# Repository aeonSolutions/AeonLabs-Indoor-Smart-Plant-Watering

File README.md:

[ ](https://discord.gg/hw3j3RwfJf)

[PCB-Prototyping-Catalogue](https://github.com/aeonSolutions/PCB-Prototyping-Catalogue)  >>   [Home-Automation](https://github.com/aeonSolutions/PCB-Prototyping-Catalogue/tree/main/Home-Automation)  >>  [Safety & Health](https://github.com/aeonSolutions/AeonLabs-Safety-Health)    >>  Indoor Smart Plant Watering

⚠️ **Start by reading the documentation first**. [Click here to open it](https://github.com/aeonSolutions/AeonLabs-Safety-Health/wiki) 

# Indoor Smart Plant Watering

**The Problem**

Anyone loves to have some plants nearby, even when living in an apartment building. However, few know, or have devices to do proper indoor plant care. The main culprit is the absence of water and dry soil.

Furthermore, nowadays is commonly found online, when reading the news, another case and victim of light aggression, in particular, using some kind of diode laser light: red, green, yellow, or blue. And more dangerous, ultraviolet (UV) or infrared (IR) lasers.

**The Idea**

This Smart Indoor plant monitoring and watering is designed to be inserted into any indoor plant vase. Is able to measure and calculate the moisture content in the vase, and when detects low water contents, activates the water pump. Is able to connect to a local home server to upload indoor temperature, humidity, and air quality measurement data. This way, the owner, can have a history record database, without the need for expensive cloud subscriptions.  Additionally, it features a 6 LED system composed of an ultraviolet LED, an Infrared LED and an RGB LED, when combined with multiple devices like this one in the same room is able to perform some basic light aggression protection from an unknown light source outside during the night & day. 

If you prefer can read this project on Autodesk's Instructables.com website, [here](https://www.instructables.com/Indoor-Smart-Plant-Watering/).

<br>

### Status

 Fully tested and working

<br>

### Known PCB bugs
This public revision of the PCB electronics has a few known small errors. 

<br>

<p align="center">

<blockquote class="twitter-tweet"><p lang="en" dir="ltr">A small update on prototyping the indoor plant monitoring smart device <a href="https://twitter.com/gardein?ref_src=twsrc%5Etfw">@gardein</a> <a href="https://t.co/ORobUAjV0F">pic.twitter.com/ORobUAjV0F</a></p>&mdash; Aeonlabs.science (@AeonlabsS) </blockquote>
</p>

<br>

<br>

## Compatibility

<p align="center">

</p>

<br>

### Made by other Makers
 - [Soil Sensor](https://github.com/GewoonMaarten/soil-sensor) by [Maarten](https://github.com/GewoonMaarten)

<br>

## What one additionally needs
- [USB to UART/USB TTL firmware burner for 5V and 3.3V MCUs ](https://github.com/aeonSolutions/PCB-Prototyping-Catalogue/blob/main/DIY-Maker/README.md) 
<br />
<br />

**Get a Notification on every PCB update**

|  | You can fill in your [email here (Google form)](https://docs.google.com/forms/d/e/1FAIpQLScErMgQYRdA-umvCjvTPPrCO7Lg1QYowTxb7vfa8cTfrcPEAA/viewform?usp=pp_url) and I'll send a reminder when a new PCB prototype is made available here or a new revision for an existing PCB. Stay tuned! |
|-------------|------|

<br />

## Buy the PRO version on Tindie

|  | To all those not into electronics and still liked and want to own any of the listed PCB for smart devices can buy the PRO version on Tindie ready to install and use. |
|-------------|------|

### Useful links 
Below is a list of links with useful information about these kinds of abusive and many times criminal and terrorist usages.
[continue reading ...](https://github.com/aeonSolutions/AeonLabs-Safety-Health/wiki/Useful-Links)

<br />
<br />

**Get a Notification on every PCB update**

|  | You can fill in your [email here (Google form)](https://docs.google.com/forms/d/e/1FAIpQLScErMgQYRdA-umvCjvTPPrCO7Lg1QYowTxb7vfa8cTfrcPEAA/viewform?usp=pp_url) and I'll send a reminder when a new PCB prototype is made available here or a new revision for an existing PCB. Stay tuned! |
|-------------|------|

<br>

**Hire AeonLabs** <br>
If you like my work here and are looking to design and deploy your own smart device find [here](https://github.com/aeonSolutions/PCB-Prototyping-Catalogue/wiki/How-to-Hire-AeonLabs) how to hire me. 

<br>

## Author

You can get in touch with me on my LinkedIn Profile:

#### Miguel Tomas

You can also follow my GitHub Profile to stay updated about my latest projects: 

<br>

### Be supportive of my dedication and work towards technology education and buy me a cup of coffee
The PCB Design Files I provide here for anyone to use are free. If you like this Smart Device or use it, please consider buying me a cup of coffee, a slice of pizza, or a book to help me study, eat, and think new PCB design files.

<br />

### Make a donation on Paypal
Make a donation on PayPal and get a TAX refund*.

### License

Before proceeding to download any of AeonLabs open source code for software solutions and/or open hardware electronics for smart devices and data acquisition make sure you are choosing the right license for your project. See [AeonLabs Solutions for Open Hardware & Open Source Code](https://github.com/aeonSolutions/PCB-Prototyping-Catalogue/wiki/AeonLabs-Solutions-for-Open-Hardware-&-Source-Development) for more information. For commercial business solutions contact AeonLabs for more information ℹ️ using the contacts above. Thank you 🙏.

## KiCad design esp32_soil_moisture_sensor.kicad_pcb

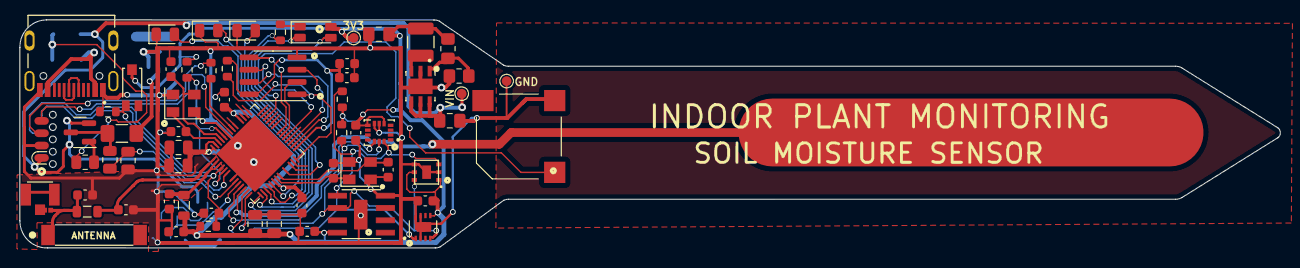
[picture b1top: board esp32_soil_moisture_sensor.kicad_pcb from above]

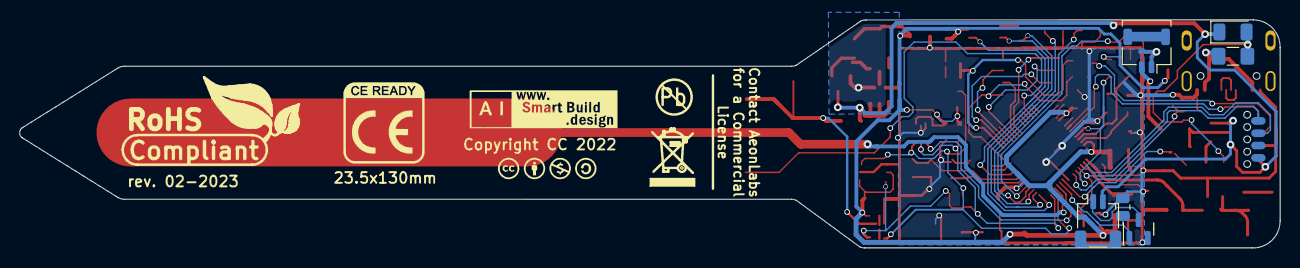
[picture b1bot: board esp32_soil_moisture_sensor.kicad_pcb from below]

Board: 2 copper layers, 129.9 x 23.5 mm, 71 parts (9 on the bottom side), 46 nets.

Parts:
AC1: 22uF; C_0805_2012Metric_Pad1.18x1.45mm_HandSolder
AC2: 4.7uF; C_0805_2012Metric_Pad1.18x1.45mm_HandSolder
AL1: 3.3uF; L_1210_3225Metric
ANT1: AN9520; AN9520_ANT2-SMD-9.5X2.1X1.0MM
AR1: 24K; R_0805_2012Metric_Pad1.20x1.40mm_HandSolder
AR2: 7k5; R_0805_2012Metric_Pad1.20x1.40mm_HandSolder
AU1: AUR9718x_DFN_3x3mm_6_pin; AUR9718 ST1S09 SON95P300X300X100-7N
AUC1: 100nF; C_0603_1608Metric
BAT2: Screw_Terminal_01x02; JST_SHL_SM02B-SHLS-TF_1x02-1MP_P1.00mm_Horizontal
BZ1: Buzzer; MagneticBuzzer_Kobitone_254-EMB84Q-RO
D12: UV LED; LED_0805_2012Metric
D13: IR LED; LED_0805_2012Metric
D14: WHITE LED; LED_0805_2012Metric
EC12, EC13, EC50, EC51: 22pF 5% 50V; C_0603_1608Metric
EC14: 100pF; C_0805_2012Metric
EC15: 1uF 10% 50V; C_0805_2012Metric
EC16, EC19, EC20, EC24, EC26, EC37, EC38: 100nF 10% 16V; C_0603_1608Metric
EC17, EC18: 10uF 20% 6.3V; C_0805_2012Metric
EC25: 1uF 10% 50V; C_0603_1608Metric
EC40: 100nF; C_0603_1608Metric
ECY1: 40Mhz 22pF+-10PPM; Crystal_SMD_EuroQuartz_MT-4Pin_3.2x2.5mm
ECY2: 32.768Mhz 22pF+-10PPM; Crystal_SMD_EuroQuartz_MT-4Pin_3.2x2.5mm
EL4: 2nH 5%; L_0805_2012Metric
EPS1: ESP32-PSRAM_LY68L6400S; SOIC-8_3.9x4.9mm_P1.27mm
ER1, ER5: 10k; R_0603_1608Metric
ER2: 499R; R_0603_1608Metric
ESP32S3: ESP32-S3; QFN-56-1EP_7x7mm_P0.4mm_EP5.6x5.6mm
F1, F2: Polyfuse; Fuse_1206_3216Metric_Pad1.42x1.75mm_HandSolder
ICR1: 10k; R_0603_1608Metric
ICSP1: Conn_01x08_Male; SOIC_clipProgSmall
IDR1: 10k; R_0603_1608Metric
IMU1: LSM6DS3; LSM6DS3 PQFN50P300X250X86-14N
IMUC1, IMUC2: 100nF; C_0603_1608Metric
J1: U.FL-R-SMT(01); HRS_U.FL-R-SMT(01)
J2: USB_C_TYPE-C-31-M-12; USB C HRO_TYPE-C-31-M-12
L2: 12nH 5%; L_0805_2012Metric
LED1: LED_GBRC; LED_1206_3210_RGB_Metric
LR1: 330R; R_0603_1608Metric
MR3: 390K; R_0805_2012Metric
MR4: 110K; R_0805_2012Metric
MTRR1: 10k; R_0805_2012Metric
MTRT1: NPN; SOT-23
PSR1: 100K; R_0603_1608Metric
PWD1: ss12; D_1206_3216Metric
PWDSWT1: S8050; SOT-23
PWSWR1: 10k; R_0805_2012Metric
SH1: SHT31-DIS; Sensirion_DFN-8-1EP_2.5x2.5mm_P0.5mm_EP1.1x1.7mm
SHJ1: Screw_Terminal_01x02; JST_SH_SM02B-SRSS-TB_1x02-1MP_P1.00mm_Horizontal
Sign-PbFree: LOGO_PBFREE
Sign-RecycleBin: LOGO_RECYCLEBIN_1
Sign-RoHS: LOGO_ROHS_1
TMPR1: 10K; R_0603_1608Metric
TP1: VIN; TestPoint_Pad_D1.0mm
TP2: VOut; TestPoint_Pad_D1.0mm
TP3: GND; TestPoint_Pad_D1.0mm
U1: TEMT6000; TEMT6000-SEN
U2: ATSHA204A-MAHDA-T; ATSHA204A Auth SOIC8
U7: SGP30

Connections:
3V3: AC1.1, AL1.1, AR1.1, AUC1.2, EC14.2, EC15.2, EC16.1, EC17.1, EC18.1, EC19.1, EC26.1, ER1.1, ER5.1, ESP32S3.20 (VDD3P3_RTC), ESP32S3.46 (VDD3P3_CPU), ESP32S3.55 (VDDA), ESP32S3.56 (VDDA), ICR1.1, IDR1.2, IMU1.5 (VDDIO), IMU1.8 (VDD), IMUC1.2, IMUC2.2, L2.1, LED1.4 (K), SH1.5 (VDD), TP2.1, U1.COLLECTOR, U2.8 (VCC), U7.1 (VDD), U7.5 (VDDH)
5V0: F2.1, PWD1.2 (A), PWSWR1.1
BAT_SENSE_IO04: ESP32S3.9 (GPIO4/ADC1_CH3), MR3.2, MR4.1
BUZZER_IO35: BZ1.1 (-), ESP32S3.40 (GPIO35)
CHIP_EN: EC40.2, ER1.2, ESP32S3.4 (CHIP_PU/RESET), ICSP1.5
DC_MOTOR_IO05: ESP32S3.10 (GPIO5/ADC1_CH4), MTRR1.2, MTRT1.1
ESP_GPIO0_BOOT-DTR: ER5.2, ESP32S3.5 (GPIO0/BOOT), ESP32S3.52 (GPIO46), ICSP1.6
GND: AC1.2, AC2.2, AR2.2, AU1.2 (GND), AU1.7 (GND), AUC1.1, BAT2.1, BZ1.2 (+), D12.1 (K), D13.1 (K), D14.1 (K), EC12.2, EC13.2, EC14.1, EC15.1, EC16.2, EC17.2, EC18.2, EC19.2, EC20.2, EC24.2, EC25.2, EC26.2, EC37.2, EC38.2, EC40.1, EC50.2, EC51.2, ECY1.2, ECY1.4, ECY2.2, ECY2.4, EPS1.4 (VSS), ESP32S3.8 (GPIO3/ADC1_CH2), ESP32S3.51 (GPIO45), ESP32S3.57 (GND), ICSP1.2, IMU1.6 (GND), IMU1.7 (GND), IMUC1.1, IMUC2.1, J2.A1B12 (GND), J2.B1A12 (GND), MR4.2, MTRR1.1, MTRT1.2, SH1.2 (ADDR), SH1.7 (R), SH1.8 (VSS), SH1.9 (VSS), TMPR1.1, TP3.1, U2.4 (GND), U7.2 (VSS), U7.4 (R)
GPIO8_I2C_SDA: ESP32S3.13 (GPIO8/ADC1_CH7), IDR1.1, IMU1.14 (SDA), SH1.1 (SDA), U2.5 (SDA), U7.3 (SDA)
GPIO9_I2C_SCL: ESP32S3.14 (GPIO9/ADC1_CH8), ICR1.2, IMU1.13 (SCL), SH1.4 (SCL), U2.6 (SCL), U7.6 (SCL)
IMU_CS_IO06: ESP32S3.11 (GPIO6/ADC1_CH5), IMU1.12 (CS)
LED_BLUE_IO18: ESP32S3.24 (GPIO18/ADC2_CH7/DAC_1), LED1.2 (BA)
LED_GREEN_IO10: ESP32S3.15 (GPIO10/ADC1_CH9), LED1.1 (GA)
LED_IR_IO12: D13.2 (A), ESP32S3.17 (GPIO12/ADC2_CH1)
LED_RED_IO11: ESP32S3.16 (GPIO11/ADC2_CH0), LR1.1
LED_UV_IO14: D12.2 (A), ESP32S3.19 (GPIO14/ADC2_CH3)
LED_WHITE_IO13: D14.2 (A), ESP32S3.18 (GPIO13/ADC2_CH2)
unnamed: AL1.2, AU1.3 (SW)
unnamed: ANT1.1, EC37.1, EL4.1
unnamed: AR1.2, AR2.1, AU1.1 (FB)
unnamed: EC12.1, ECY1.1, ESP32S3.54 (XTAL_P)
unnamed: EC13.1, ECY1.3, ESP32S3.53 (XTAL_N)
unnamed: EC20.1, ESP32S3.2 (VDD3P3), ESP32S3.3 (VDD3P3), L2.2
unnamed: EC38.1, EL4.2, ESP32S3.1 (LNA_IN/RF)
unnamed: EC50.1, ECY2.1, ESP32S3.21 (GPIO15/ADC2_CH4/XTAL_32K_P)
unnamed: EC51.1, ECY2.3, ESP32S3.22 (GPIO16/ADC2_CH5/XTAL_32K_N)
unnamed: ER2.2, ESP32S3.49 (U0TXD/PROG/GPIO43)
unnamed: LED1.3 (RA), LR1.2
unnamed: MTRT1.3, SHJ1.1
unnamed: PWDSWT1.1, PWSWR1.2
RXD0: ESP32S3.50 (U0RXD/PROG/GPIO44), ICSP1.4
SPICLK: EPS1.6 (SCLK), ESP32S3.33 (SPICLK/GPIO30)
SPICS1: EPS1.1 (~CE), ESP32S3.28 (SPI_CS1/GPIO26), PSR1.1
SPID: EPS1.5 (SiO0), ESP32S3.35 (SPID/GPIO32)
SPIHD: EPS1.7 (SIO3), ESP32S3.30 (SPIHD/GPIO27)
SPIQ: EPS1.2 (SIO1), ESP32S3.34 (SPIQ/GPIO31)
SPIWP: EPS1.3 (SIO2), ESP32S3.31 (SPIWP/GPIO28)
TEMT6000_IO01: ESP32S3.6 (GPIO1/ADC1_CH0), TMPR1.2, U1.EMITTER
TXD0: ER2.1, ICSP1.3
USB_D+: J2.A6 (DP1), J2.B6 (DP2)
USB_D-: J2.A7 (DN1), J2.B7 (DN2)
VDD_SPI: EC24.1, EC25.1, EPS1.8 (VCC), ESP32S3.29 (VDD_SPI), PSR1.2
VIN_AUR: AC2.1, AU1.4 (VIN_SW), AU1.5 (VIN_A), AU1.6 (EN), ICSP1.1, PWD1.1 (K), PWDSWT1.2, SHJ1.2, TP1.1
VIN_BAT: F1.1, MR3.1, PWDSWT1.3
VIN_BATF: BAT2.2, F1.2
VIN_USBF: F2.2, J2.A4B9 (VBUS), J2.B4A9 (VBUS)

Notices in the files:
esp32_soil_moisture_sensor.kicad_pcb:
Copyright CC 2022
